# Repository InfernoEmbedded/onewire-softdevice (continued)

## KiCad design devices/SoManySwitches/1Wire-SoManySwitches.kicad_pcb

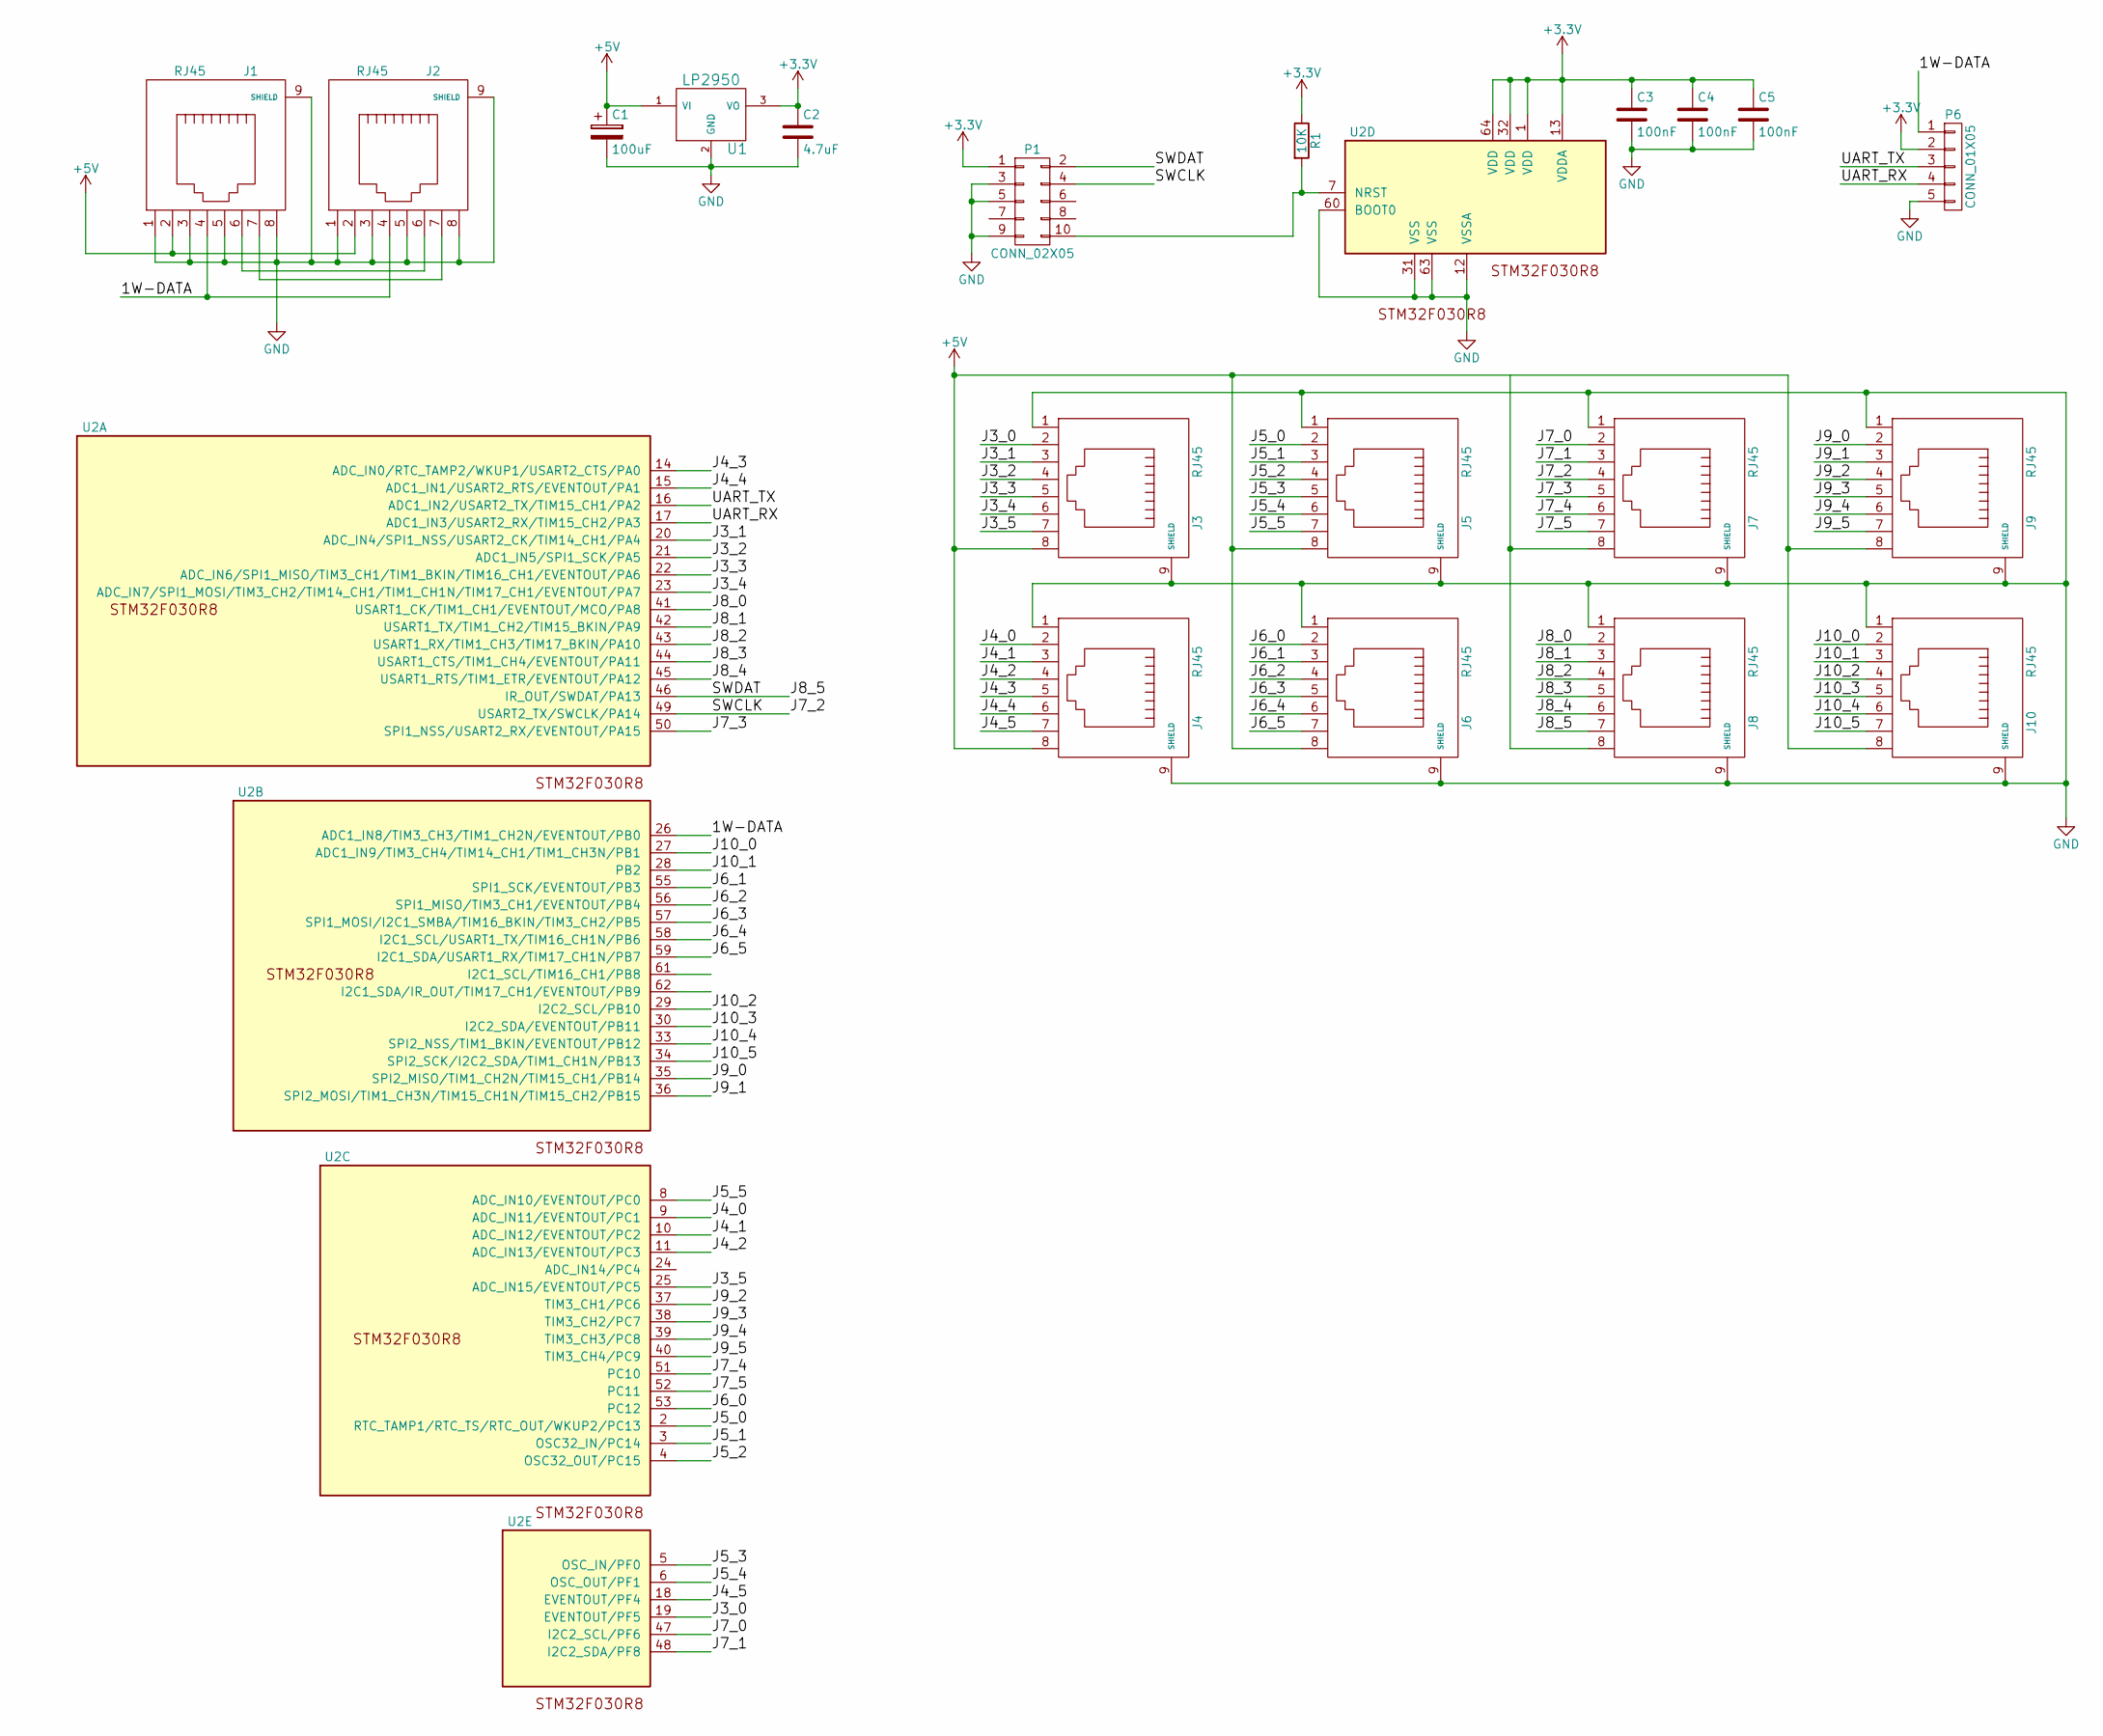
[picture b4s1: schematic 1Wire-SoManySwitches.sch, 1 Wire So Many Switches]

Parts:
C1: 100uF; c_elec_8x6.7
C2: 4.7uF; C_0603
C3, C4, C5: 100nF; C_0603
J1, J2, J3, J4, J5, J6, J7, J8, J9, J10: RJ45; RJ45-ChinaSMD
P1: CONN_02X05; Pin_Header_Straight_SMT_02x05
P6: CONN_01X05; Pin_Header_Straight_1x05_Pitch2.54mm
R1: 10K; R_0603
U1: LP2950; TO-252-2Lead
U2: STM32F030R8; LQFP-64_10x10mm_Pitch0.5mm

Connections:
+3V3: C2.1, C3.1, C4.1, C5.1, P1.1, P6.2, R1.1, U1.3 (VO), U2.1 (VDD), U2.13 (VDDA), U2.32 (VDD), U2.64 (VDD)
+5V: C1.1, J1.2, J2.2, J3.8, J4.8, J5.8, J6.8, J9.8, J10.8, U1.1 (VI)
/1W-DATA: J1.4, J2.4, P6.1, U2.26 (ADC1_IN8/TIM3_CH3/TIM1_CH2N/EVENTOUT/PB0)
/J3_0: J3.2, U2.19 (EVENTOUT/PF5)
/J3_1: J3.3, U2.20 (ADC_IN4/SPI1_NSS/USART2_CK/TIM14_CH1/PA4)
/J3_2: J3.4, U2.21 (ADC1_IN5/SPI1_SCK/PA5)
/J3_3: J3.5, U2.22 (ADC_IN6/SPI1_MISO/TIM3_CH1/TIM1_BKIN/TI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)
/J3_4: J3.6, U2.23 (ADC_IN7/SPI1_MOSI/TIM3_CH2/TIM14_CH1/TI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)
/J3_5: J3.7, U2.25 (ADC_IN15/EVENTOUT/PC5)
/J4_0: J4.2, U2.9 (ADC_IN11/EVENTOUT/PC1)
/J4_1: J4.3, U2.10 (ADC_IN12/EVENTOUT/PC2)
/J4_2: J4.4, U2.11 (ADC_IN13/EVENTOUT/PC3)
/J4_3: J4.5, U2.14 (ADC_IN0/RTC_TAMP2/WKUP1/USART2_CTS/PA0)
/J4_4: J4.6, U2.15 (ADC1_IN1/USART2_RTS/EVENTOUT/PA1)
/J4_5: J4.7, U2.18 (EVENTOUT/PF4)
/J5_0: J5.2, U2.2 (RTC_TAMP1/RTC_TS/RTC_OUT/WKUP2/PC13)
/J5_1: J5.3, U2.3 (OSC32_IN/PC14)
/J5_2: J5.4, U2.4 (OSC32_OUT/PC15)
/J5_3: J5.5, U2.5 (OSC_IN/PF0)
/J5_4: J5.6, U2.6 (OSC_OUT/PF1)
/J5_5: J5.7, U2.8 (ADC_IN10/EVENTOUT/PC0)
/J6_0: J6.2, U2.53 (PC12)
/J6_1: J6.3, U2.55 (SPI1_SCK/EVENTOUT/PB3)
/J6_2: J6.4, U2.56 (SPI1_MISO/TIM3_CH1/EVENTOUT/PB4)
/J6_3: J6.5, U2.57 (SPI1_MOSI/I2C1_SMBA/TIM16_BKIN/TIM3_CH2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)
/J6_4: J6.6, U2.58 (I2C1_SCL/USART1_TX/TIM16_CH1N/PB6)
/J6_5: J6.7, U2.59 (I2C1_SDA/USART1_RX/TIM17_CH1N/PB7)
/J7_0: J7.2, U2.47 (I2C2_SCL/PF6)
/J7_1: J7.3, U2.48 (I2C2_SDA/PF8)
/J7_2: J7.4, P1.4, U2.49 (USART2_TX/SWCLK/PA14)
/J7_3: J7.5, U2.50 (SPI1_NSS/USART2_RX/EVENTOUT/PA15)
/J7_4: J7.6, U2.51 (PC10)
/J7_5: J7.7, U2.52 (PC11)
/J8_0: J8.2, U2.41 (USART1_CK/TIM1_CH1/EVENTOUT/MCO/PA8)
/J8_1: J8.3, U2.42 (USART1_TX/TIM1_CH2/TIM15_BKIN/PA9)
/J8_2: J8.4, U2.43 (USART1_RX/TIM1_CH3/TIM17_BKIN/PA10)
/J8_3: J8.5, U2.44 (USART1_CTS/TIM1_CH4/EVENTOUT/PA11)
/J8_4: J8.6, U2.45 (USART1_RTS/TIM1_ETR/EVENTOUT/PA12)
/J8_5: J8.7, P1.2, U2.46 (IR_OUT/SWDAT/PA13)
/J9_0: J9.2, U2.35 (SPI2_MISO/TIM1_CH2N/TIM15_CH1/PB14)
/J9_1: J9.3, U2.36 (SPI2_MOSI/TIM1_CH3N/TIM15_CH1N/TIM15_CH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)
/J9_2: J9.4, U2.37 (TIM3_CH1/PC6)
/J9_3: J9.5, U2.38 (TIM3_CH2/PC7)
/J9_4: J9.6, U2.39 (TIM3_CH3/PC8)
/J9_5: J9.7, U2.40 (TIM3_CH4/PC9)
/J10_0: J10.2, U2.27 (ADC1_IN9/TIM3_CH4/TIM14_CH1/TIM1_CH3N/P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)
/J10_1: J10.3, U2.28 (PB2)
/J10_2: J10.4, U2.29 (I2C2_SCL/PB10)
/J10_3: J10.5, U2.30 (I2C2_SDA/EVENTOUT/PB11)
/J10_4: J10.6, U2.33 (SPI2_NSS/TIM1_BKIN/EVENTOUT/PB12)
/J10_5: J10.7, U2.34 (SPI2_SCK/I2C2_SDA/TIM1_CH1N/PB13)
/UART_RX: P6.4, U2.17 (ADC1_IN3/USART2_RX/TIM15_CH2/PA3)
/UART_TX: P6.3, U2.16 (ADC1_IN2/USART2_TX/TIM15_CH1/PA2)
GND: C1.2, C2.2, C3.2, C4.2, C5.2, J1.1, J1.3, J1.5, J1.8, J1.9 (SHIELD), J2.1, J2.3, J2.5, J2.8, J2.9 (SHIELD), J3.1, J3.9 (SHIELD), J4.1, J4.9 (SHIELD), J5.1, J5.9 (SHIELD), J6.1, J6.9 (SHIELD), J7.1, J7.9 (SHIELD), J8.1, J8.9 (SHIELD), J9.1, J9.9 (SHIELD), J10.1, J10.9 (SHIELD), P1.3, P1.5, P1.9, P6.5, U1.2 (GND), U2.12 (VSSA), U2.31 (VSS), U2.60 (BOOT0), U2.63 (VSS)
unnamed: J1.6, J2.6
unnamed: J1.7, J2.7
unnamed: J7.8, J8.8
unnamed: P1.10, R1.2, U2.7 (NRST)

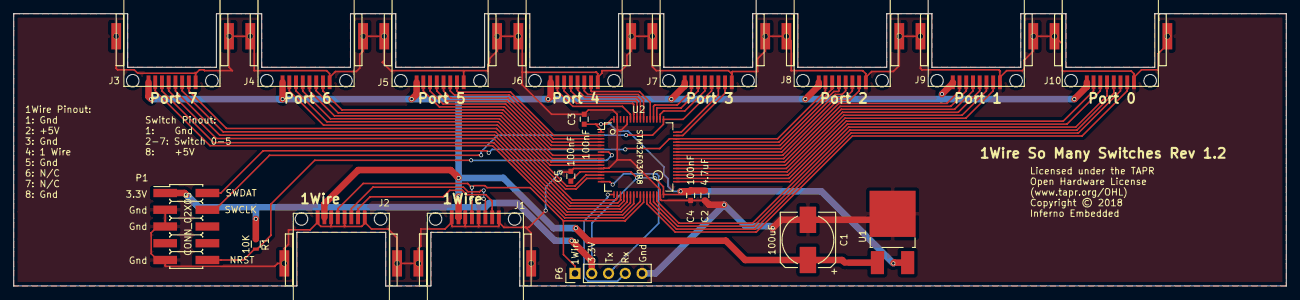
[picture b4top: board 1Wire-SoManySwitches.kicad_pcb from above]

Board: 2 copper layers, 192.9 x 41.3 mm, 20 parts (0 on the bottom side), 58 nets.

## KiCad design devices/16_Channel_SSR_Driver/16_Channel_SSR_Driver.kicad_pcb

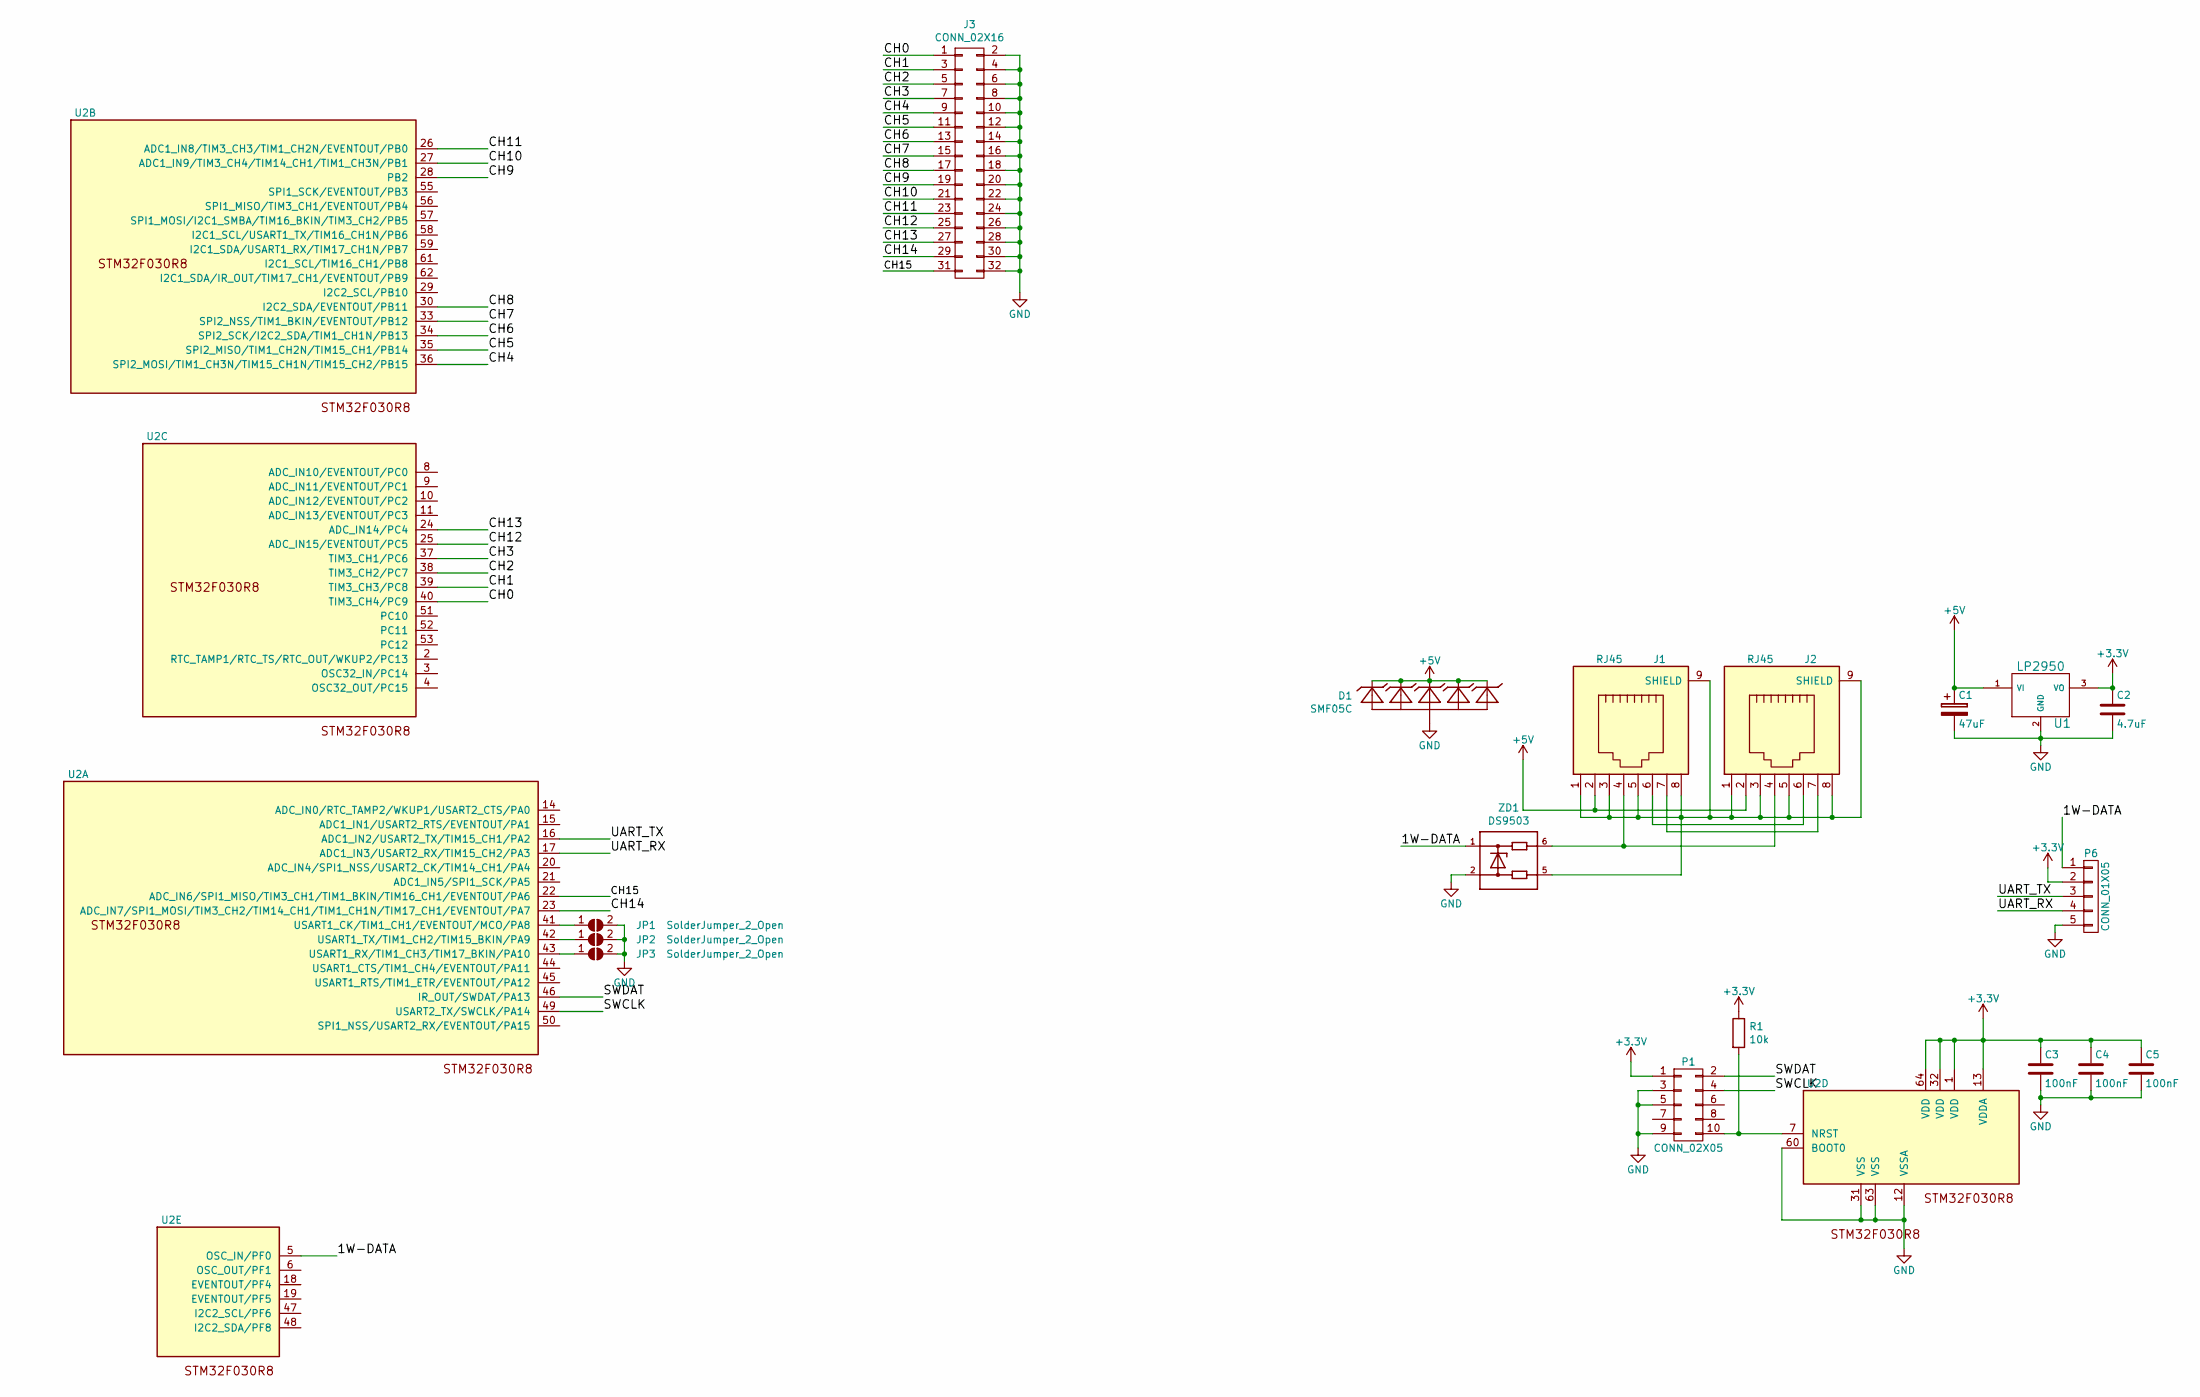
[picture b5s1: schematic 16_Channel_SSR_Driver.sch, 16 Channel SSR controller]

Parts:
C1: 47uF; C_1206
C2: 4.7uF; C_0603
C3, C4, C5: 100nF; C_0603
D1: SMF05C; SC70-6
J1, J2: RJ45; RJ45-ChinaSMD
J3: CONN_02X16; Pin_Header_Straight_2x16_Pitch2.54mm_SMD
JP1, JP2, JP3: SolderJumper_2_Open; JUMPER_0805
P1: CONN_02X05; Pin_Header_Straight_2x05_Pitch2.54mm_SMD
P6: CONN_01X05; Pin_Header_Straight_1x05_Pitch2.54mm
R1: 10k; R_0603
U1: LP2950; TO-252-2
U2: STM32F030R8; LQFP-64_10x10mm_Pitch0.5mm
ZD1: DS9503; TSOC6

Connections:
+3V3: C2.1, C3.1, C4.1, C5.1, P1.1, P6.2, R1.1, U1.3 (VO), U2.1 (VDD), U2.13 (VDDA), U2.32 (VDD), U2.64 (VDD)
+5V: C1.1, D1.1 (C1), D1.3 (C2), D1.4 (C3), D1.5 (C4), D1.6 (C5), J1.2, J2.2, U1.1 (VI)
/1W-DATA: P6.1, U2.5 (OSC_IN/PF0), ZD1.1
/CH0: J3.1, U2.40 (TIM3_CH4/PC9)
/CH1: J3.3, U2.39 (TIM3_CH3/PC8)
/CH2: J3.5, U2.38 (TIM3_CH2/PC7)
/CH3: J3.7, U2.37 (TIM3_CH1/PC6)
/CH4: J3.9, U2.36 (SPI2_MOSI/TIM1_CH3N/TIM15_CH1N/TIM15_CH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)
/CH5: J3.11, U2.35 (SPI2_MISO/TIM1_CH2N/TIM15_CH1/PB14)
/CH6: J3.13, U2.34 (SPI2_SCK/I2C2_SDA/TIM1_CH1N/PB13)
/CH7: J3.15, U2.33 (SPI2_NSS/TIM1_BKIN/EVENTOUT/PB12)
/CH8: J3.17, U2.30 (I2C2_SDA/EVENTOUT/PB11)
/CH9: J3.19, U2.28 (PB2)
/CH10: J3.21, U2.27 (ADC1_IN9/TIM3_CH4/TIM14_CH1/TIM1_CH3N/P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)
/CH11: J3.23, U2.26 (ADC1_IN8/TIM3_CH3/TIM1_CH2N/EVENTOUT/PB0)
/CH12: J3.25, U2.25 (ADC_IN15/EVENTOUT/PC5)
/CH13: J3.27, U2.24 (ADC_IN14/PC4)
/CH14: J3.29, U2.23 (ADC_IN7/SPI1_MOSI/TIM3_CH2/TIM14_CH1/TI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)
/CH15: J3.31, U2.22 (ADC_IN6/SPI1_MISO/TIM3_CH1/TIM1_BKIN/TI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)
/SWCLK: P1.4, U2.49 (USART2_TX/SWCLK/PA14)
/SWDAT: P1.2, U2.46 (IR_OUT/SWDAT/PA13)
/UART_RX: P6.4, U2.17 (ADC1_IN3/USART2_RX/TIM15_CH2/PA3)
/UART_TX: P6.3, U2.16 (ADC1_IN2/USART2_TX/TIM15_CH1/PA2)
GND: C1.2, C2.2, C3.2, C4.2, C5.2, D1.2 (A), J3.2, J3.4, J3.6, J3.8, J3.10, J3.12, J3.14, J3.16, J3.18, J3.20, J3.22, J3.24, J3.26, J3.28, J3.30, J3.32, JP1.2 (B), JP2.2 (B), JP3.2 (B), P1.3, P1.5, P1.9, P6.5, U1.2 (GND), U2.12 (VSSA), U2.31 (VSS), U2.60 (BOOT0), U2.63 (VSS), ZD1.2
unnamed: J1.1, J1.3, J1.5, J1.8, J1.9 (SHIELD), J2.1, J2.3, J2.5, J2.8, J2.9 (SHIELD), ZD1.5
unnamed: J1.4, J2.4, ZD1.6
unnamed: J1.6, J2.6
unnamed: J1.7, J2.7
unnamed: JP1.1 (A), U2.41 (USART1_CK/TIM1_CH1/EVENTOUT/MCO/PA8)
unnamed: JP2.1 (A), U2.42 (USART1_TX/TIM1_CH2/TIM15_BKIN/PA9)
unnamed: JP3.1 (A), U2.43 (USART1_RX/TIM1_CH3/TIM17_BKIN/PA10)
unnamed: P1.10, R1.2, U2.7 (NRST)

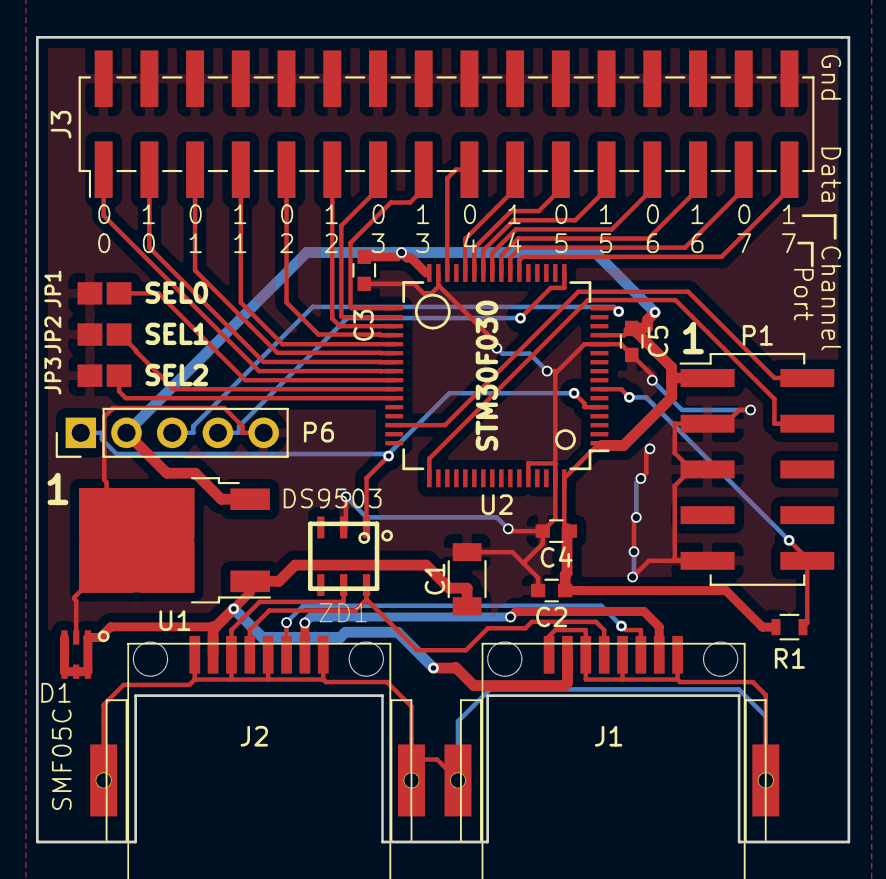
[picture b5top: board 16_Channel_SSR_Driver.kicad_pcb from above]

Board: 2 copper layers, 45.1 x 44.7 mm, 18 parts (0 on the bottom side), 32 nets.

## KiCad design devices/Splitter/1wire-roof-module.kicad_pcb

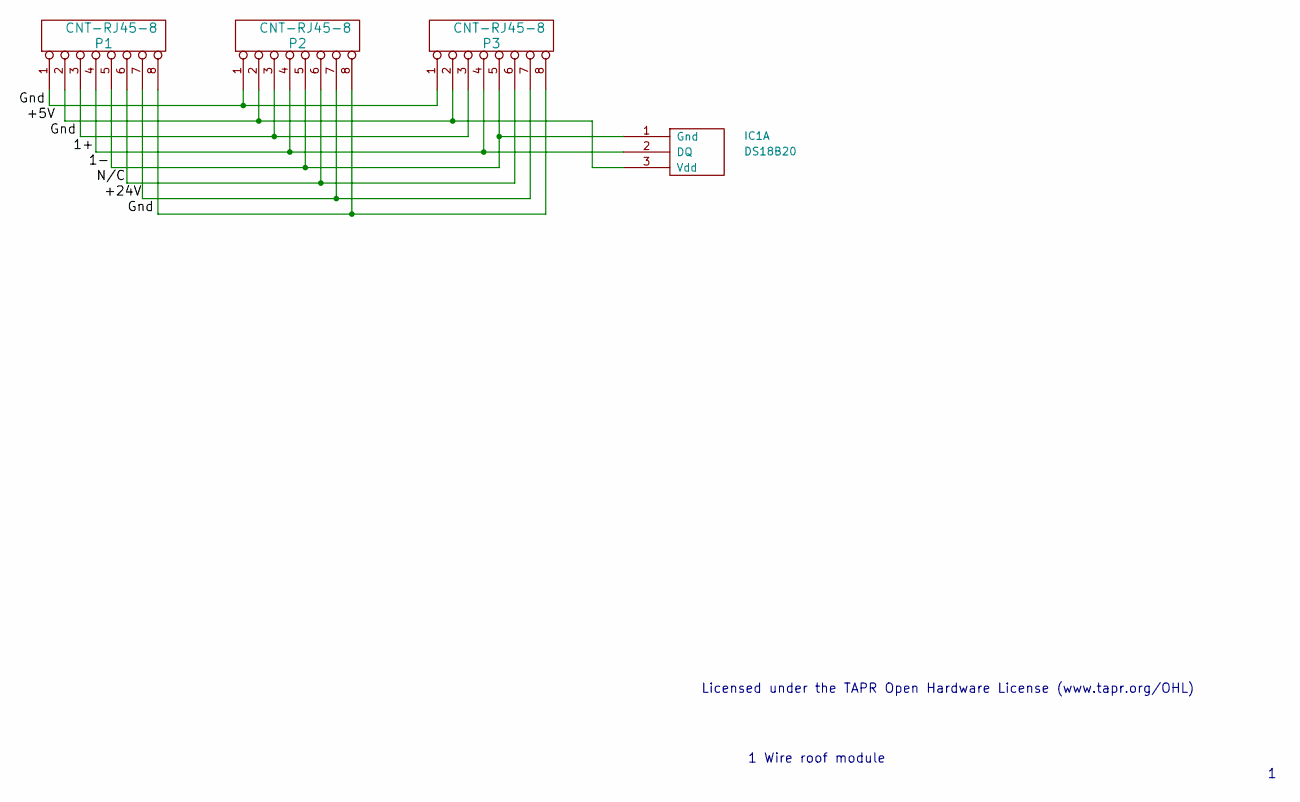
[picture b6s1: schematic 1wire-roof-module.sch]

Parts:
IC1: DS18B20; 1wire-TO92-
P1, P2, P3: CNT-RJ45-8

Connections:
unnamed: P1.1, P2.1, P3.1
unnamed: P1.8, P2.8, P3.8
unnamed: P1.7, P2.7, P3.7
unnamed: P1.6, P2.6, P3.6
unnamed: IC1.1 (Gnd), P1.5, P2.5, P3.5
unnamed: P1.3, P2.3, P3.3
unnamed: IC1.2 (DQ), P1.4, P2.4, P3.4
unnamed: IC1.3 (Vdd), P1.2, P2.2, P3.2

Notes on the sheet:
1 Wire roof module
Licensed under the TAPR Open Hardware License (www.tapr.org/OHL)

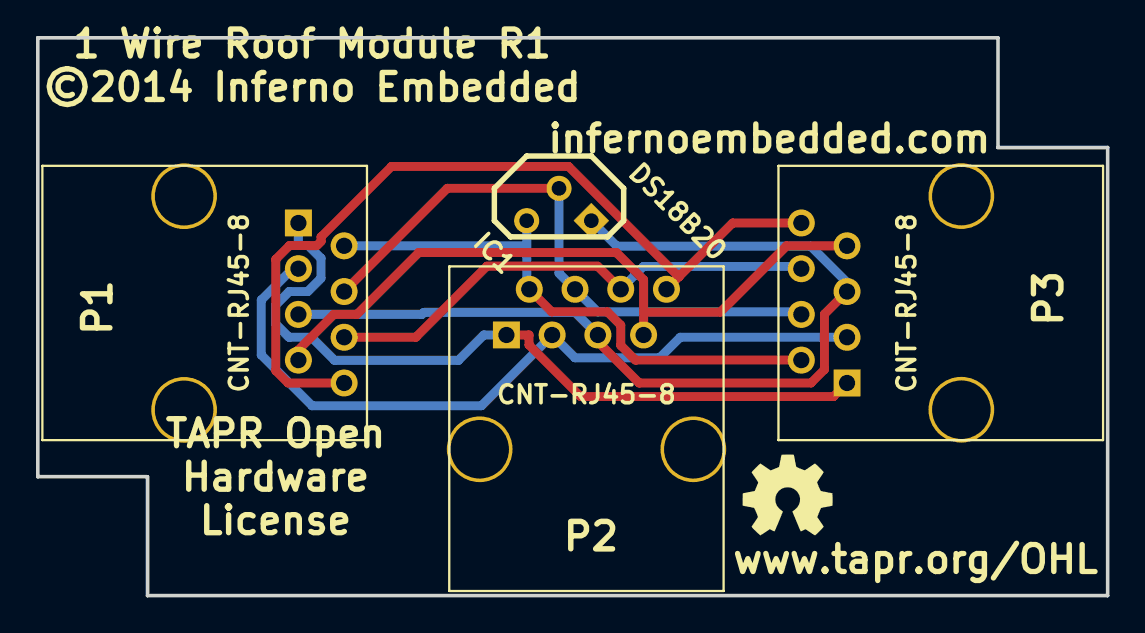
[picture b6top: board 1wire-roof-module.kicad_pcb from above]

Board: 2 copper layers, 59.4 x 31.0 mm, 4 parts (0 on the bottom side), 8 nets.

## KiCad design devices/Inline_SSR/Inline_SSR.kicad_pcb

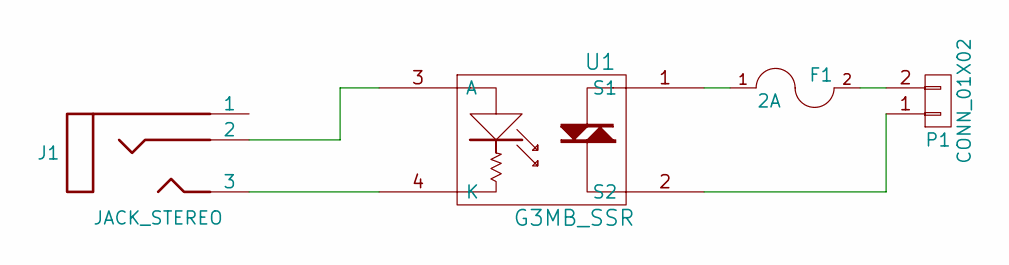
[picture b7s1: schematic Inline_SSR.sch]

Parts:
F1: 2A; Fuse_0679H
J1: JACK_STEREO; jack_3.5_pj313d-smt
P1: CONN_01X02; 2EDCK-5.08-2PIN
U1: G3MB_SSR; G3MB

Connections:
unnamed: F1.1, U1.1 (S1)
unnamed: F1.2, P1.2
unnamed: J1.2, U1.3 (A)
unnamed: J1.3, U1.4 (K)
unnamed: P1.1, U1.2 (S2)

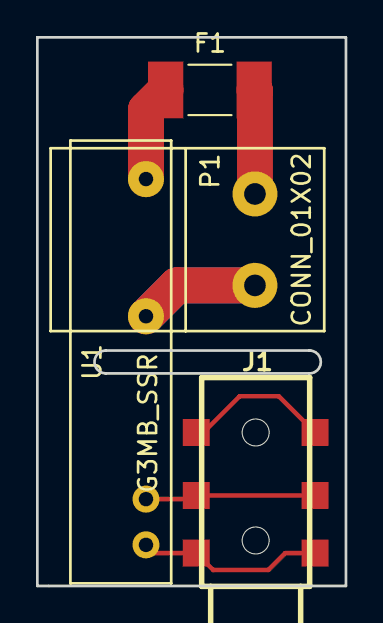
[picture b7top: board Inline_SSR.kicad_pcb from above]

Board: 2 copper layers, 17.1 x 30.5 mm, 4 parts (0 on the bottom side), 5 nets.

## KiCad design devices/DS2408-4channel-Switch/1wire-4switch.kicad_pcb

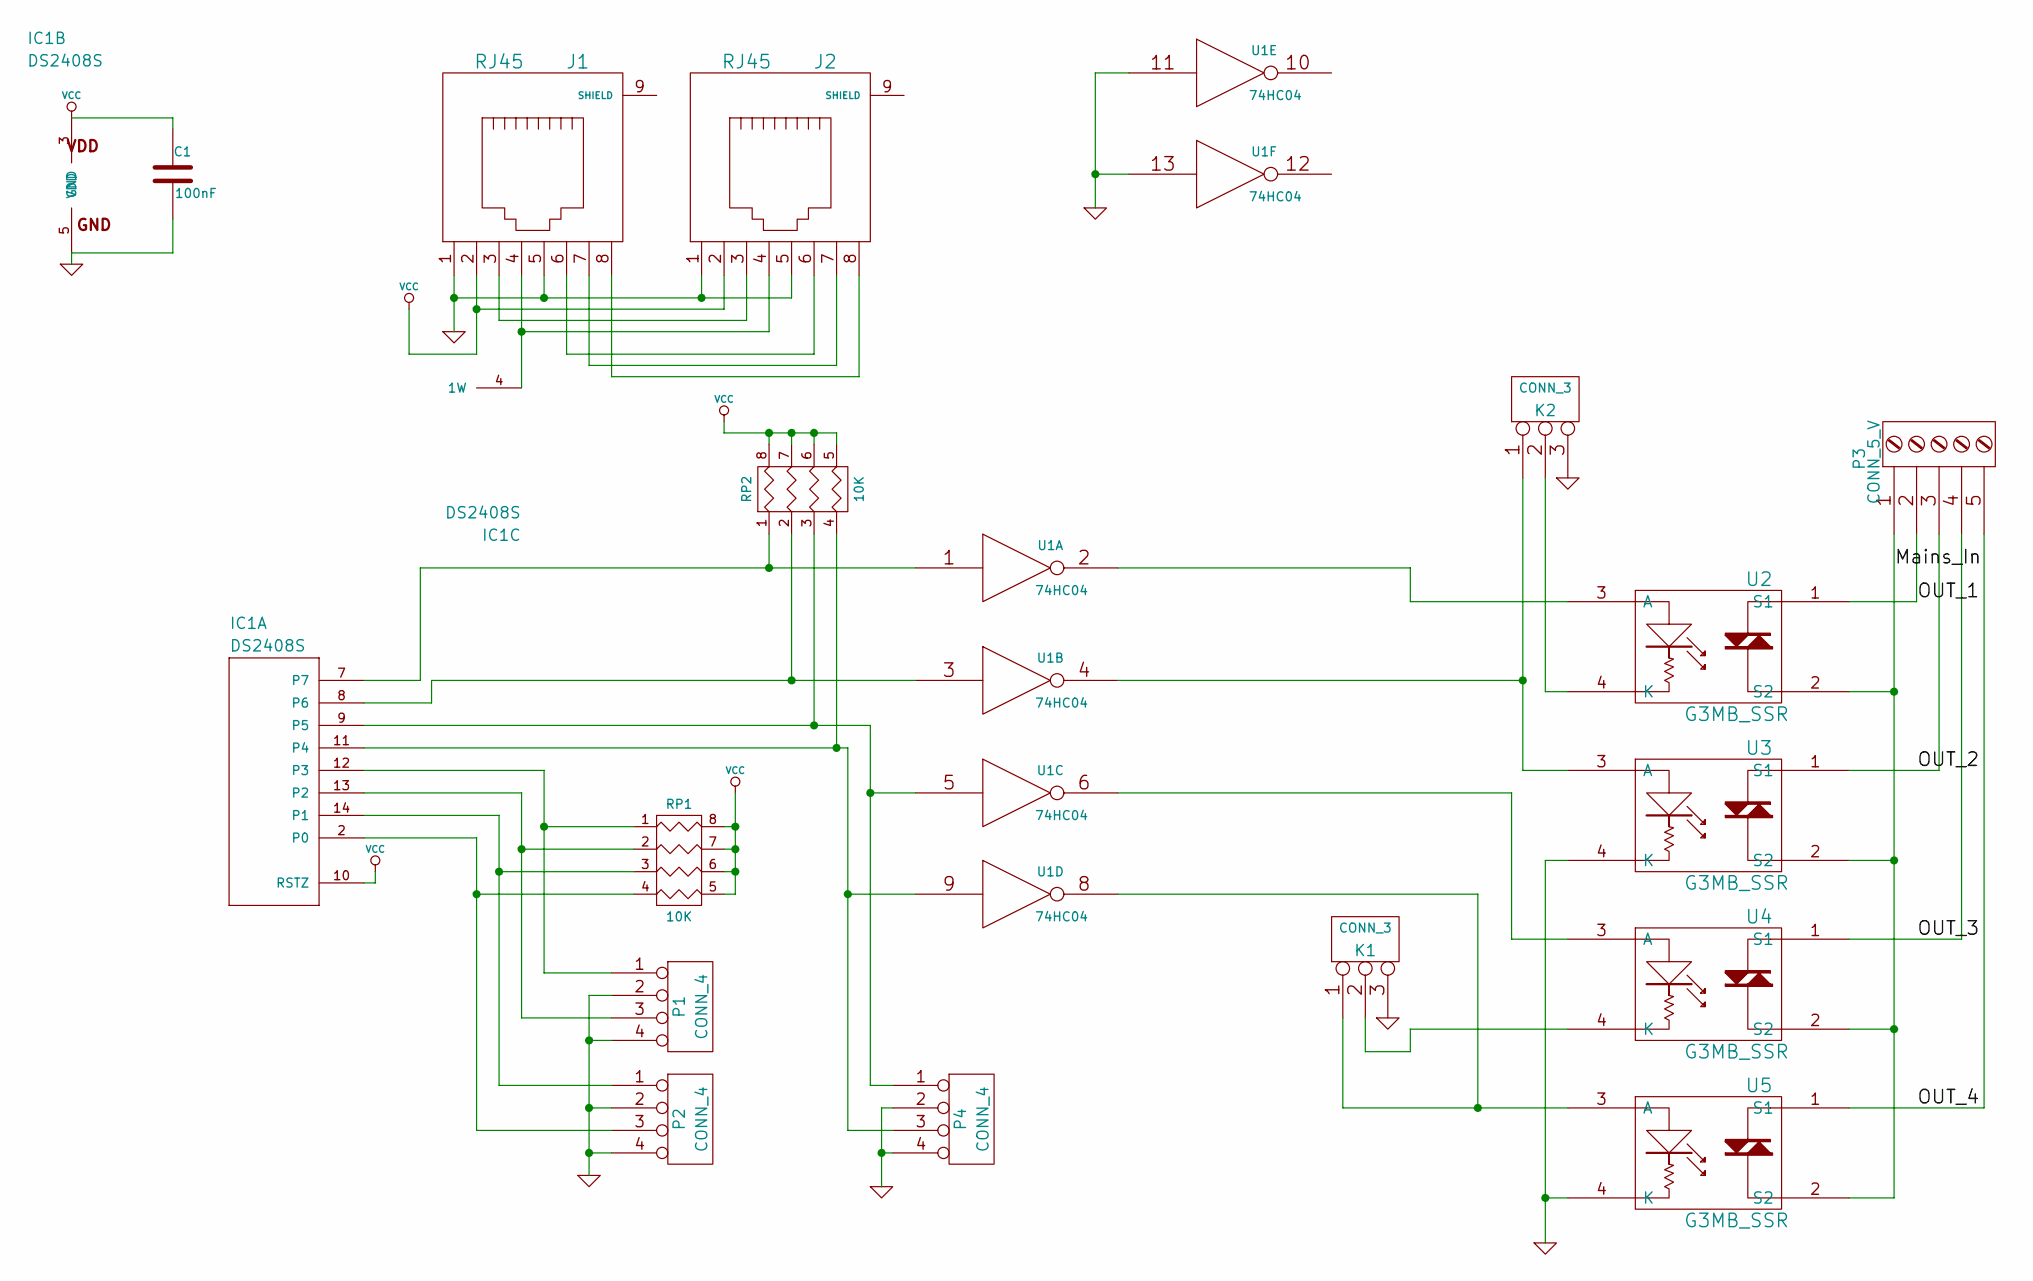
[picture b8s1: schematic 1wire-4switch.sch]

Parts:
C1: 100nF
IC1: DS2408S; 1wire-SO16
J1, J2: RJ45
K1, K2: CONN_3
P1, P2, P4: CONN_4
P3: CONN_5_V
RP1, RP2: 10K
U1: 74HC04
U2, U3, U4, U5: G3MB_SSR

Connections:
/Mains_In: P3.1, U2.2 (S2), U3.2 (S2), U4.2 (S2), U5.2 (S2)
/OUT_1: P3.2, U2.1 (S1)
/OUT_2: P3.3, U3.1 (S1)
/OUT_3: P3.4, U4.1 (S1)
/OUT_4: P3.5, U5.1 (S1)
GND: C1.2, IC1.5 (GND), J1.1, J1.5, J2.1, J2.5, K1.3, K2.3, P1.2, P1.4, P2.2, P2.4, P4.2, P4.4, U1.7 (GND), U1.11, U1.13, U3.4 (K), U5.4 (K)
unnamed: K1.1, U1.8, U5.3 (A)
unnamed: U1.6, U4.3 (A)
unnamed: IC1.7, RP2.1, U1.1
unnamed: K1.2 (PM), U4.4 (K)
unnamed: K2.1, U1.4, U3.3 (A)
unnamed: U1.2, U2.3 (A)
unnamed: K2.2 (PM), U2.4 (K)
unnamed: IC1.11 (P4), P4.3, RP2.4, U1.9
unnamed: IC1.9 (P5), P4.1, RP2.3, U1.5
unnamed: IC1.8 (P6), RP2.2, U1.3
unnamed: J1.8, J2.8
unnamed: J1.7, J2.7
unnamed: J1.6, J2.6
unnamed: IC1.4 (1W), J1.4, J2.4
unnamed: IC1.12 (P3), P1.1, RP1.1
unnamed: J1.3, J2.3
unnamed: IC1.2 (P0), P2.3, RP1.4
unnamed: IC1.14 (P1), P2.1, RP1.3
unnamed: IC1.13 (P2), P1.3, RP1.2
VCC: C1.1, IC1.3 (VDD), IC1.10 (RSTZ), J1.2, J2.2, RP1.5 (R4), RP1.6 (R3), RP1.7 (R2), RP1.8 (R1), RP2.5 (R4), RP2.6 (R3), RP2.7 (R2), RP2.8 (R1), U1.14 (VCC)

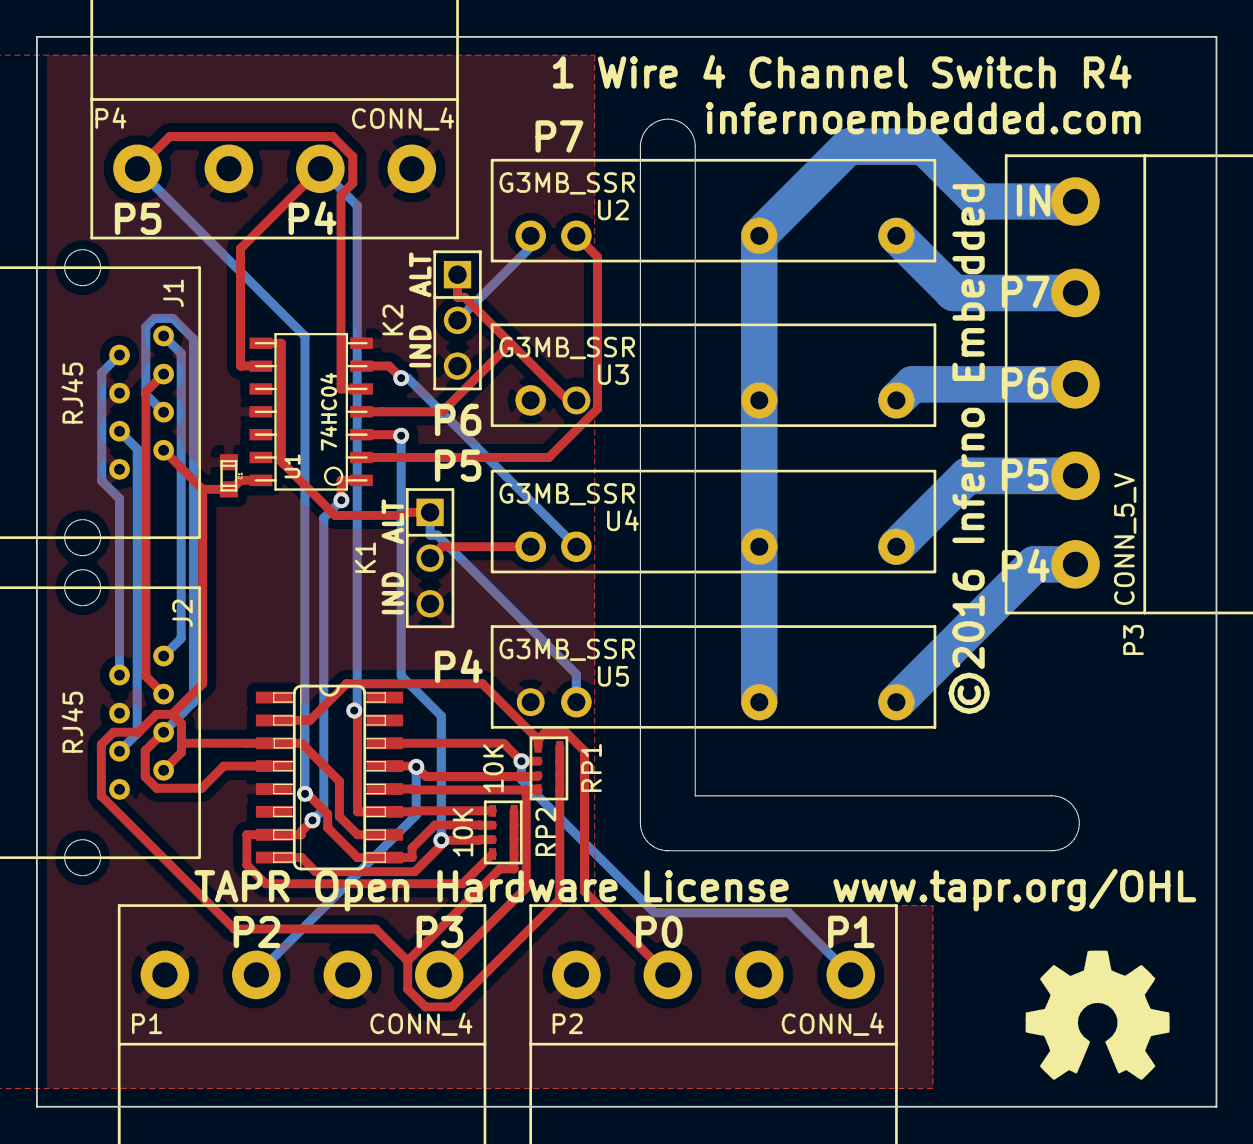
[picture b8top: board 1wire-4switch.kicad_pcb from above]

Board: 2 copper layers, 65.5 x 59.4 mm, 17 parts (0 on the bottom side), 26 nets.

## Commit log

2014-08-05 Add 1Wire roof module
2014-08-05 Add 1Wire 4 way switch/SSR module
2014-08-19 Increased hole size for connectors Compacted the board a little bit RJ45 sockets now overhang the board in order to sit flust with the case
2014-09-19 Commit Revision 3 of the board (fabbed)
2014-09-19 Move back the external connectors to afford more clearance for right angled connectors Fix the reversed pinouts on the PJ45 connectors
2014-09-19 Restore cutout to edge-cuts Tidy silkscreen
2016-05-08 Increase SSR holes for easier installation
2017-02-26 Initial commit of 2 channel RGBW Controller, fabbed as Rev 1.0
2017-02-26 LED Controller: Remove clock crystal (internal RC oscillator is good enough) Add a current limiting resistor to +5V to keep newly connecting devices from browning out the rail Move serial port no USA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
2017-02-26 1Wire LED Controller Fix footprint of LP2950 voltage regulator Add a 1wire test point on the serial header
2017-06-03 Add 4 channel RGBW LED controller
2017-06-03 Add gitignore
2017-06-03 Remove backup files
2017-06-03 Remove stray gerber archives
2017-06-03 Bring the 4 channel switch module up to date
2017-06-03 Ignore .old files
2017-06-03 Bring the roof splitter module up to date
2017-06-03 Add template 1Wire slave project
2017-06-03 Add 1 Wire 8 channel aircon zone controller
2017-06-03 Add SoManySwitches 8x6 switch controller
2017-06-03 Ignore .g and .orig files
2017-06-03 Add OneWireSlave base library
2017-06-03 Add DS2408 emulation example
2017-06-03 Add bootloader for updating firmware over 1wire
2017-06-03 Add firmware for 4 Channel RGBW LED controller
2017-06-03 Add firmware for the SoManySwitches 8x6 switch device
2017-06-03 Add Air Conditioning Zone controller firmware
2017-06-03 Add Eclipse project files & build scripts for Mbed
2017-06-03 Move hardware projects to the hardware directory
2017-06-03 Create a devices directory and group schematics & source code by device
2017-06-03 Ignore build products
2017-06-03 Tweak release config for OneWireSlave
2017-06-03 Add licenses
2017-06-03 Add Readme
2017-06-03 Tweak table rendering in Readme
2017-06-03 Expand hardware info in readme
2017-06-03 Add the Inline SSR board for external mains switching
2017-06-08 Refactor SwitchMaster to support On/Off zone pairs
2017-06-08 Remove ACZoneController (obsoleted by SwitchMaster enhancements)
2017-06-12 Add 4 Channel SSR module with 8 inputs
2017-06-12 switchHasBeenActivated must be public
2017-06-12 Ignore Spectra files used for autorouting
2017-06-12 Update eclipse files
2017-06-12 Use auxilary axis origin for GerberPanelizer
2017-06-12 Remove stray file
2017-06-12 Use templated SwitchMaster
2017-06-12 Add missing gerber
2017-06-26 Add control & output boards for a 32 Channel 1 Wire master for the Orange Pi Prime
2017-08-08 Add pullups to the PiMultichannelMaster outputboard pullup mosfet
2018-11-19 Use family code 0xED instead of 0xFE to avoid collision
2018-11-30 Recreate mbed-os as a git submodule
2018-11-30 Add script to build a suitable arm-nano-eabi toolchain
2018-12-06 Build the toolchain as arm-none-eabi, in the toolchain directory
2018-12-06 Big cleanup/upgrade of Kicad files
2018-12-10 Build Custom MBED platforms
    Rather than trying to pass 0-defined variables to mbed, which is
    unsupported, use a custom platform instead.
2018-12-10 Get the OneWireSlave library building with the embedded toolchain
2018-12-10 WIP< Build FirmwareUpdater
2018-12-12 Use gcc-ar to build the static library
2018-12-12 Work in progress
2018-12-12 Crosstool-ng build script
2018-12-13 Use custom patches for mbed
2018-12-19 Remove crosstool-ng for now
2018-12-22 Build mbed using the official ARM toolchain
2018-12-22 Build OneWireSlave using the official toolchain
2018-12-22 Build FirmwareUpdate with the official toolchain
2018-12-22 Get all child projects working with the latest mbed & toolchain
2018-12-22 Save pre-built firmware
2018-12-22 Add initial source for 15 Channel SSR driver
2018-12-23 Build 15 Channel SSR Driver using mbed-cli
2018-12-23 Save known-good FirmwareUpdater binaries
2018-12-23 Build FirmwareUpdater using mbed-cli
2018-12-23 Remove old mbed dir
2018-12-23 Swallow false reset pulse at the end of presence detection
    Since the pinFall() call is hidden at the start of the presence
    detection pulse, we must swallow the false long pulse starting
    from the start of the reset pulse and ending at the end of
    the presence detection pulse.
2018-12-23 Bump all active boards to Revision 1.2
    - Remove dropping resistor from 5V power line
    - Add pullup resistor to Reset line
    - Add pin markings to STM32 chip footprint
2018-12-23 Ignore more temp files
2018-12-23 Update 15 Channel SSR controller to 16 Channels, Rev 1.2
    - Add extra channel to allow for 8 pairs of channels
    - Remove series resistor on power supply
    - Add pullup resistor to reset line
2018-12-23 Update remaining projects to mbed-cli & commit firmware binaries
2018-12-23 Update AC Zone Controller to KiCAD 5
2018-12-27 Explicitly state that the documentation is under GPL
2019-01-02 Use GCC 8 from ARM
2019-01-15 Add a test program to check for shorted pins on the 16ch SSR board
2019-01-16 Fix incorrect comment for commandCountRelays
2019-01-16 Remove unused global var & fix bad address init check
2019-01-16 Add ERASE_PAGE command to firmware updater
2019-01-16 Allow SwitchMasters to have variable numbers of channels
2019-01-16 Fix for broken Timer implementations
    On some (possibly fake?) hardware, the timer counter does not wrap,
    but instead resets to 0 and stops incrementing.
    Work around these dodgy timers by restarting the timer hardware
    each time we want to measure a pulse duration.
2019-01-19 Avoid reassigning the IRQ handler away from gpioIrqHandler
    Since all Px_0 pins share a physical interrupt, we can end up with the
    IRQ handler set incorrectly.
    Reset the IRQ handler so that we are in a known good state.
2019-01-19 Clear the bits to write on a SEARCH_ROM command
    If there are bits left unwritten, then we will communicate garbage data
    back to the master.
2019-01-19 Update all prebuilt firmware with the latest OneWire fixes
2019-01-30 Add assembly and testing instructions for 16ch_SSR
2019-04-08 Fix missing interrupt handler
    The TIM15 IRQ handler was not being overidden with the strong
    symbol defined in main.
    Instead, set it at runtime with NVIC_SetVector().
2019-04-08 Remove -ffuction-sections from CFLAGS
    This is obsoleted by LTO, and can result in premature elimination
    of functions where the references and not obvious (eg. wrapped
    functions).
2019-04-08 Add build infrastructure for 2 channel & 4 channel RGBW LED Controllers
2019-04-08 GetChannel was returning the wrong channel data
    Return the channel requested, rather than channel 0.
2019-04-10 Fix serial output for 2 channel RGBW LED Controller
2019-04-10 Fix RGBW LED Controller GetChannel() & type promotion errors
    GetChannel was return the raw gamma corrected value, rather
    than the linear value the user requested.
    Move the gamma correction within the PWM driver and save the
    user requested value to report back later.
    When fading down the LEDs, a type promotion issue caused the
    values to wrap mid-cycle.
2021-11-09 Update README.md
    https://forum.kicad.info/t/warning-avoid-all-links-to-kicad-pcb-org-use-kicad-org/31521
2021-11-10 Replace link to kicad-pcb.org
